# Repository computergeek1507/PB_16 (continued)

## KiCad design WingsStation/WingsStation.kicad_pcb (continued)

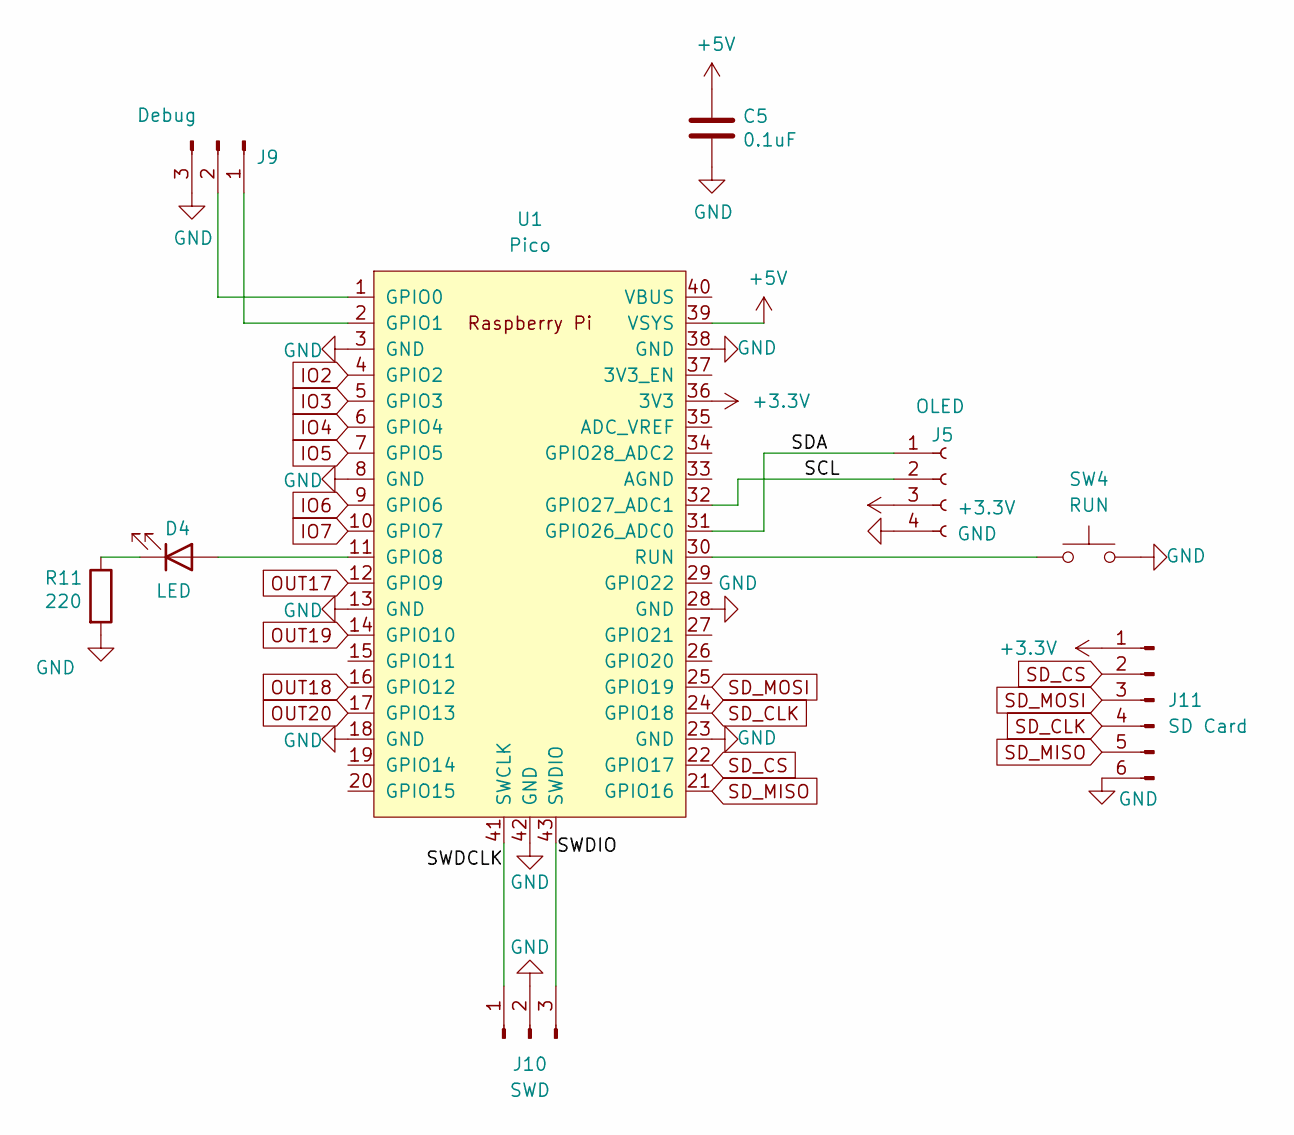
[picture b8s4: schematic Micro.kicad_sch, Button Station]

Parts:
C5: 0.1uF; C_0603_1608Metric_Pad1.08x0.95mm_HandSolder; MPN CL10B104KB8NNWC; Digi-Key_PN 1276-1935-2-ND
D4: LED; LED_0603_1608Metric_Pad1.05x0.95mm_HandSolder; MPN 150080RS75000; Digi-Key_PN 732-4984-1-ND
J5: OLED; OLED-SSD1306-128X64-I2C-THT; MPN PPTC041LFBN-RC; Digi-Key_PN S7002-ND
J9: Debug; PinHeader_1x03_P2.54mm_Vertical; MPN 61300311121; Digi-Key_PN 732-5316-ND
J10: SWD; 1x03_Horizontal_SMD
J11: SD Card; PinHeader_1x06_P2.54mm_Vertical
R11: 220; R_0603_1608Metric_Pad0.98x0.95mm_HandSolder; MPN RMCF0603FT220R; Digi-Key_PN RMCF0603FT220RTR-ND
SW4: RUN; SW_Push_1P1T_NO_6x6mm_H9.5mm; MPN PTS645SL50SMTR92 LFS; Digi-Key_PN CKN9088CT-ND
U1: Pico; RPi_Pico_SMD_TH; MPN 2648-SC0915CT-ND; Digi-Key_PN SC0915

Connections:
+3V3: J5.3, J11.1, U1.36 (3V3)
+5V: C5.1, U1.39 (VSYS); also elsewhere on the board
/Micro/SCL: J5.2, U1.32 (GPIO27_ADC1)
/Micro/SDA: J5.1, U1.31 (GPIO26_ADC0)
/Micro/SWDCLK: J10.1, U1.41 (SWCLK)
/Micro/SWDIO: J10.3, U1.43 (SWDIO)
GND: C5.2, J5.4, J9.3, J10.2, J11.6, R11.2, SW4.2, U1.3 (GND), U1.8 (GND), U1.13 (GND), U1.18 (GND), U1.23 (GND), U1.28 (GND), U1.38 (GND), U1.42 (GND); also elsewhere on the board
IO2: U1.4 (GPIO2); also elsewhere on the board
IO3: U1.5 (GPIO3); also elsewhere on the board
IO4: U1.6 (GPIO4); also elsewhere on the board
IO5: U1.7 (GPIO5); also elsewhere on the board
IO6: U1.9 (GPIO6); also elsewhere on the board
IO7: U1.10 (GPIO7); also elsewhere on the board
unnamed: D4.2 (A), U1.11 (GPIO8)
unnamed: D4.1 (K), R11.1
unnamed: J9.1, U1.2 (GPIO1)
unnamed: J9.2, U1.1 (GPIO0)
unnamed: SW4.1, U1.30 (RUN)
OUT17: U1.12 (GPIO9); also elsewhere on the board
OUT18: U1.16 (GPIO12); also elsewhere on the board
OUT19: U1.14 (GPIO10); also elsewhere on the board
OUT20: U1.17 (GPIO13); also elsewhere on the board
SD_CLK: J11.4, U1.24 (GPIO18)
SD_CS: J11.2, U1.22 (GPIO17)
SD_MISO: J11.5, U1.21 (GPIO16)
SD_MOSI: J11.3, U1.25 (GPIO19)

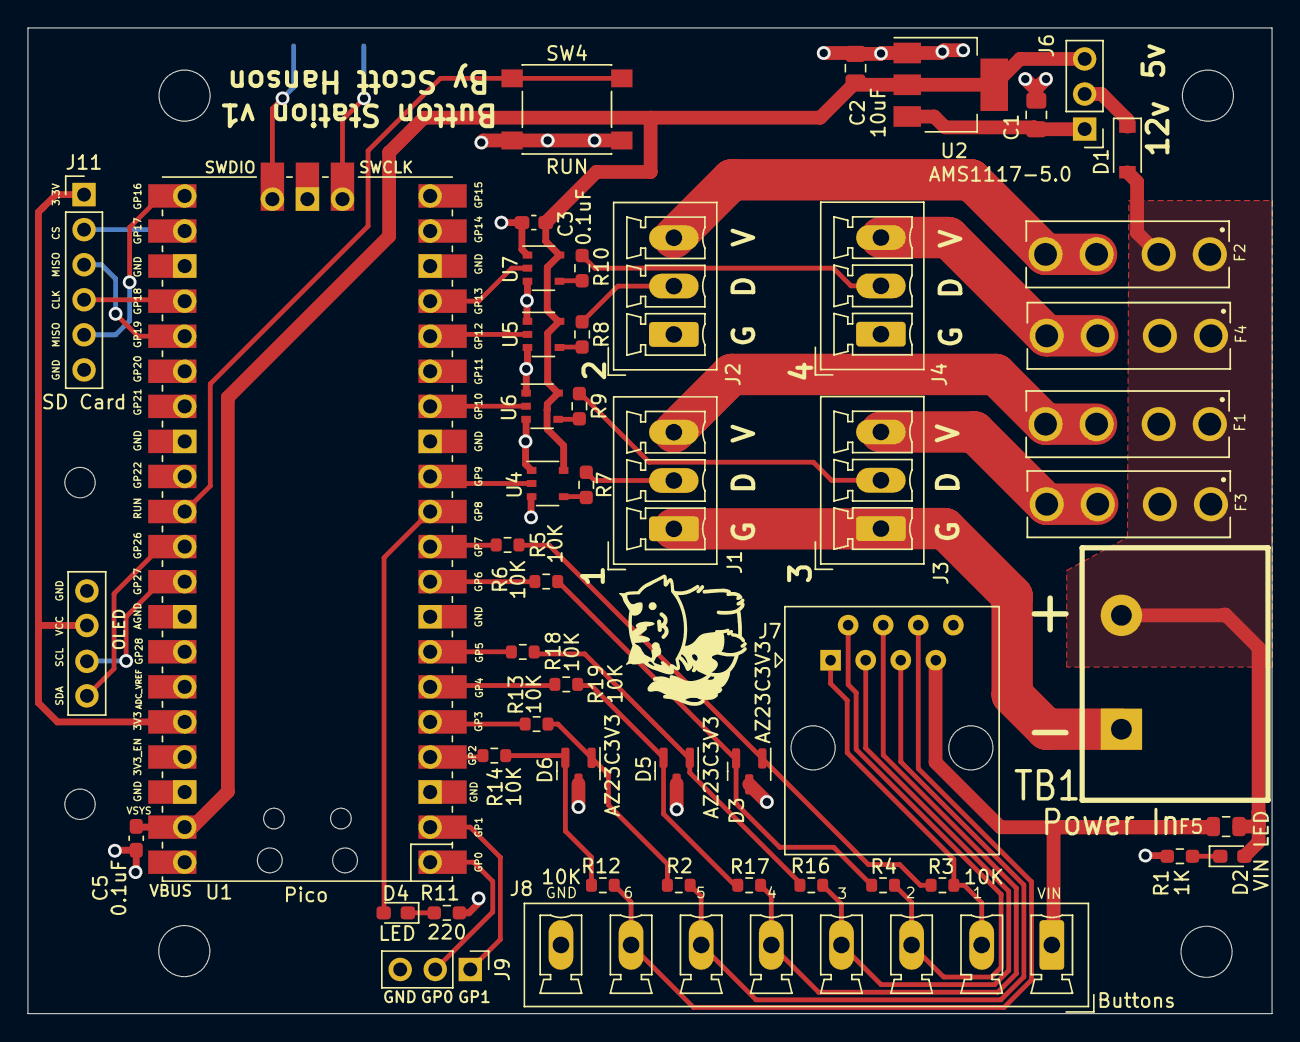
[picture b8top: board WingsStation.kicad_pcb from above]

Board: 2 copper layers, 90.1 x 71.4 mm, 56 parts (1 on the bottom side), 55 nets.

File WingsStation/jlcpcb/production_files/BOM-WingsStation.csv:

Comment,Designator,Footprint,LCSC,Quantity
RUN,SW4,SW_Push_1P1T_NO_6x6mm_H9.5mm,C127509,1
0.1uF,"C3,C5",C_0603_1608Metric_Pad1.08x0.95mm_HandSolder,C14663,2
10uF,"C1,C2",C_0805_2012Metric_Pad1.18x1.45mm_HandSolder,C15850,2
String1,"J1,J2,J3,J4","PhoenixContact_MCV_1,5_3-G-3.5_1x03_P3.50mm_Vertical",C192778,4
1K,R1,R_0603_1608Metric_Pad0.98x0.95mm_HandSolder,C21190,1
OLED,J5,OLED-SSD1306-128X64-I2C-THT,C225501,1
VIN LED,"D2,D4",LED_0603_1608Metric_Pad1.05x0.95mm_HandSolder,C2286,2
220,R11,R_0603_1608Metric_Pad0.98x0.95mm_HandSolder,C22962,1
33ohm,"R10,R7,R8,R9",R_0603_1608Metric_Pad0.98x0.95mm_HandSolder,C23140,4
10K,"R12,R13,R14,R16,R17,R18,R19,R2,R3,R4,R5,R6",R_0603_1608Metric,C25804,12
Button_Fuse,F5,Fuse_0805_2012Metric,C261938,1
RJ45,J7,RJ45_Amphenol_54602-x08_Horizontal,C2938579,1
Power In,TB1,BARRIER_BLOCK_1ROW_2POS,C306200,1
SD Card,J11,PinHeader_1x06_P2.54mm_Vertical,C37208,1
VIN_Voltage,"J6,J9",PinHeader_1x03_P2.54mm_Vertical,C49257,2
3544-2,"F1,F2,F3,F4",FUSE_3544-2,C492610,4
AMS1117-5.0,U2,SOT-223-3_TabPin2,C6187,1
Pico,U1,RPi_Pico_SMD_TH,C7203002,1
74AHCT1G125,"U4,U5,U6,U7",TSOP-5_1.65x3.05mm_P0.95mm,C7484,4
B5819W,D1,D_SOD-123,C8598,1
AZ23C3V3,"D3,D5,D6",SOT-23,C968007,3
Buttons,J8,"PhoenixContact_MCV_1,5_8-G-5.08_1x08_P5.08mm_Vertical",,1
SWD,J10,1x03_Horizontal_SMD,,1
